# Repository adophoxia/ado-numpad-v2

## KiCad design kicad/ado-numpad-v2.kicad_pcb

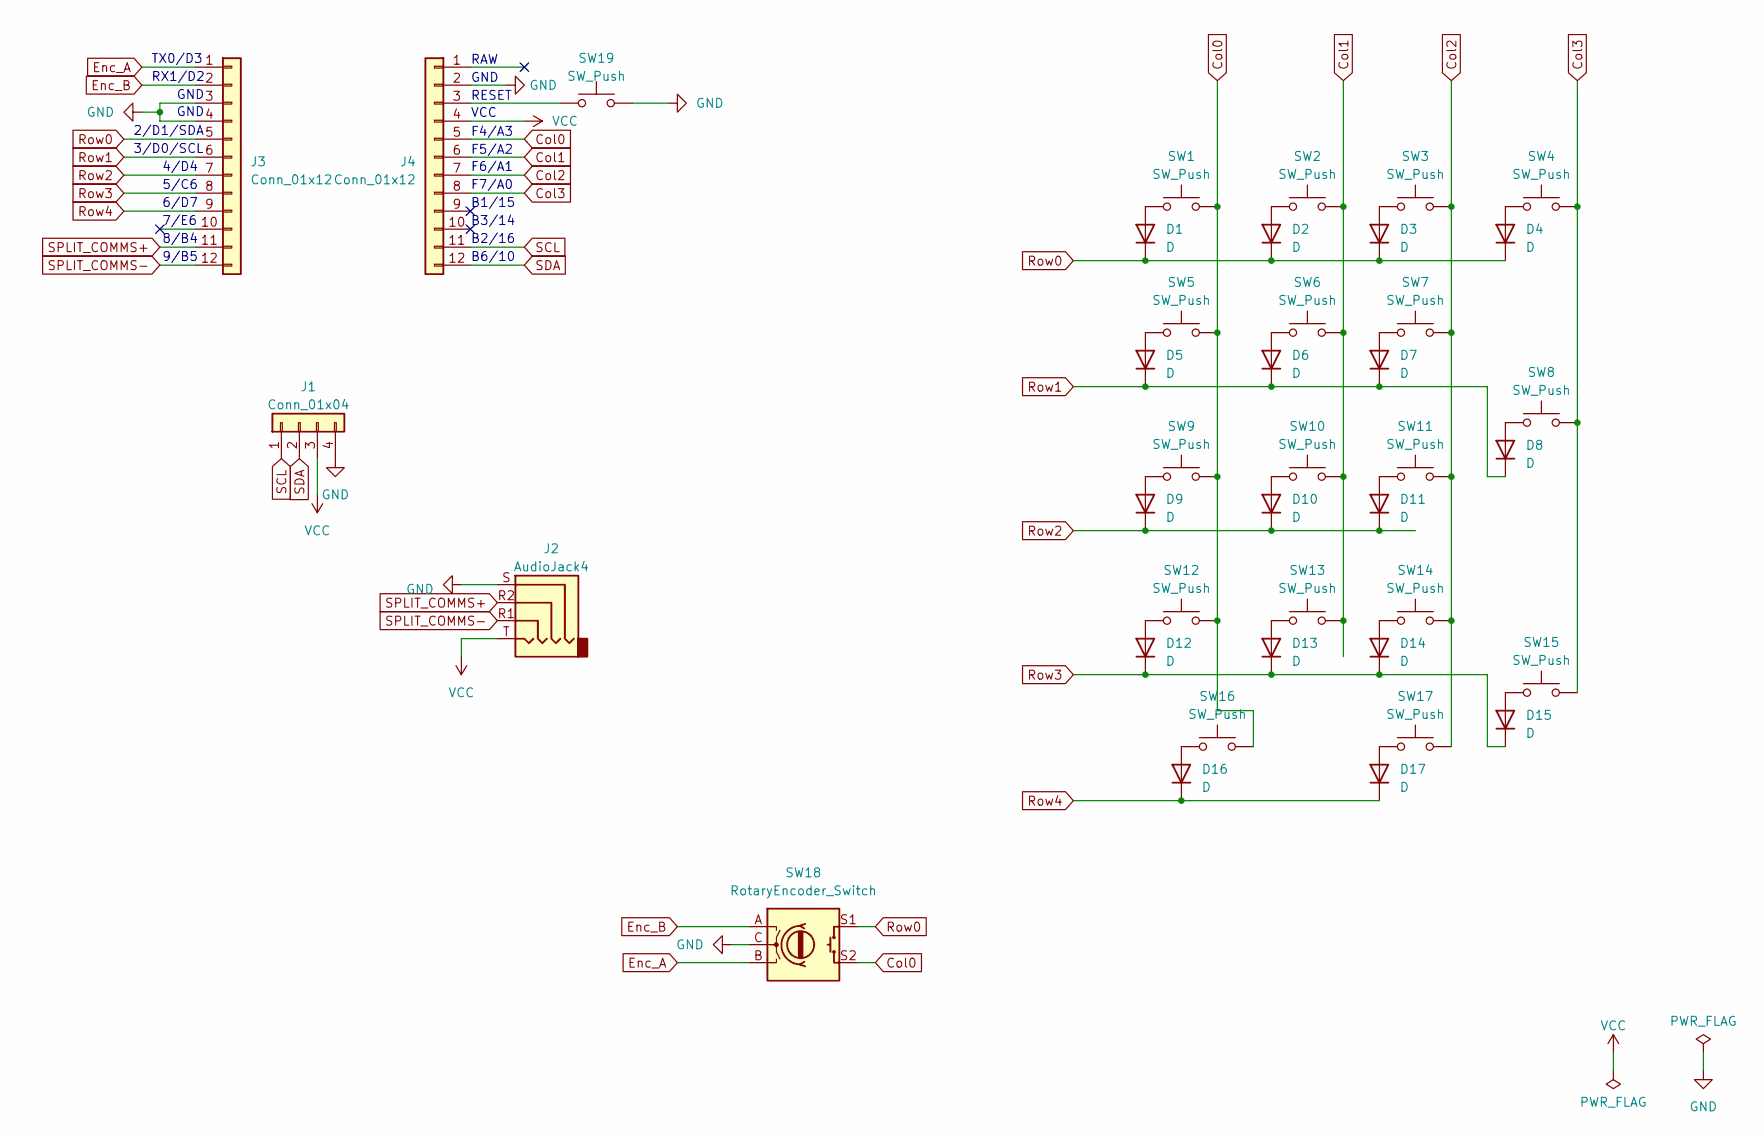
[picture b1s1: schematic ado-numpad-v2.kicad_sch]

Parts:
D1, D2, D3, D4, D5, D6, D7, D8, D9, D10, D11, D12, D13, D14, D15, D16, D17: D; D_DO-35_SOD27_P7.62mm_Horizontal
J1: Conn_01x04; PinSocket_1x04_P2.54mm_Vertical
J2: AudioJack4; Jack_3.5mm_KoreanHropartsElec_PJ-320D-4A_Horizontal
J3, J4: Conn_01x12; PinSocket_1x12_P2.54mm_Vertical
SW1, SW2, SW3, SW4, SW5, SW6, SW7, SW9, SW10, SW11, SW12, SW13, SW14, SW17: SW_Push; MX-Hotswap-1U
SW8, SW15, SW16: SW_Push; MX-Hotswap-2U-ReversedStabilizers
SW18: RotaryEncoder_Switch; RotaryEncoder_Alps_EC11E-Switch_Vertical_H20mm
SW19: SW_Push; SW_SPST_SKQG_WithStem

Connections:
Col0: J4.5, SW1.2, SW5.2, SW9.2, SW12.2, SW16.2, SW18.S2
Col1: J4.6, SW2.2, SW6.2, SW10.2, SW13.2
Col2: J4.7, SW3.2, SW7.2, SW11.2, SW14.2, SW17.2
Col3: J4.8, SW4.2, SW8.2, SW15.2
Enc_A: J3.1, SW18.B
Enc_B: J3.2, SW18.A
GND: J1.4, J2.S, J3.3, J3.4, J4.2, SW18.C, SW19.1
unnamed: D1.2 (A), SW1.1
unnamed: D2.2 (A), SW2.1
unnamed: D3.2 (A), SW3.1
unnamed: D4.2 (A), SW4.1
unnamed: D5.2 (A), SW5.1
unnamed: D6.2 (A), SW6.1
unnamed: D7.2 (A), SW7.1
unnamed: D8.2 (A), SW8.1
unnamed: D9.2 (A), SW9.1
unnamed: D10.2 (A), SW10.1
unnamed: D11.2 (A), SW11.1
unnamed: D12.2 (A), SW12.1
unnamed: D13.2 (A), SW13.1
unnamed: D14.2 (A), SW14.1
unnamed: D15.2 (A), SW15.1
unnamed: D16.2 (A), SW16.1
unnamed: D17.2 (A), SW17.1
unnamed: J4.3, SW19.2
Row0: D1.1 (K), D2.1 (K), D3.1 (K), D4.1 (K), J3.5, SW18.S1
Row1: D5.1 (K), D6.1 (K), D7.1 (K), D8.1 (K), J3.6
Row2: D9.1 (K), D10.1 (K), D11.1 (K), J3.7
Row3: D12.1 (K), D13.1 (K), D14.1 (K), D15.1 (K), J3.8
Row4: D16.1 (K), D17.1 (K), J3.9
SCL: J1.1, J4.11
SDA: J1.2, J4.12
SPLIT_COMMS+: J2.R2, J3.11
SPLIT_COMMS-: J2.R1, J3.12
VCC: J1.3, J2.T, J4.4

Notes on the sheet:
8/B4
3/D0/SCL
F7/A0
F6/A1
5/C6
B1/15
VCC
9/B5
GND
RAW
B3/14
B6/10
RESET
F4/A3
RX1/D2
2/D1/SDA
B2/16
6/D7
F5/A2
7/E6
4/D4
TX0/D3

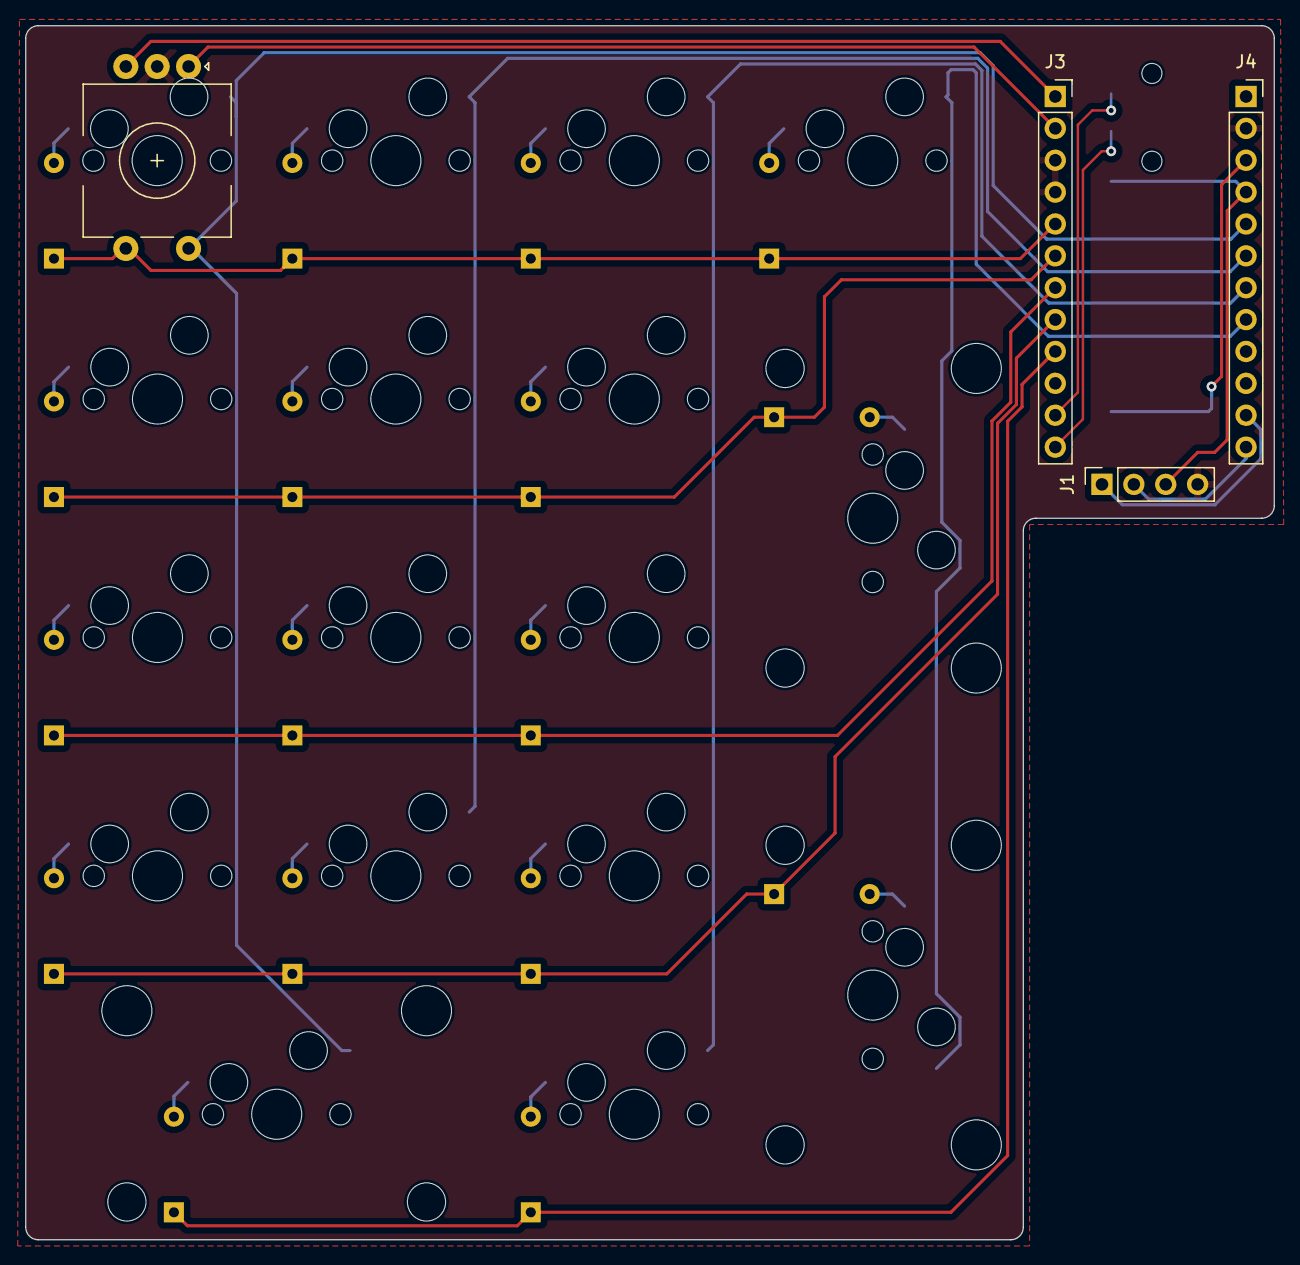
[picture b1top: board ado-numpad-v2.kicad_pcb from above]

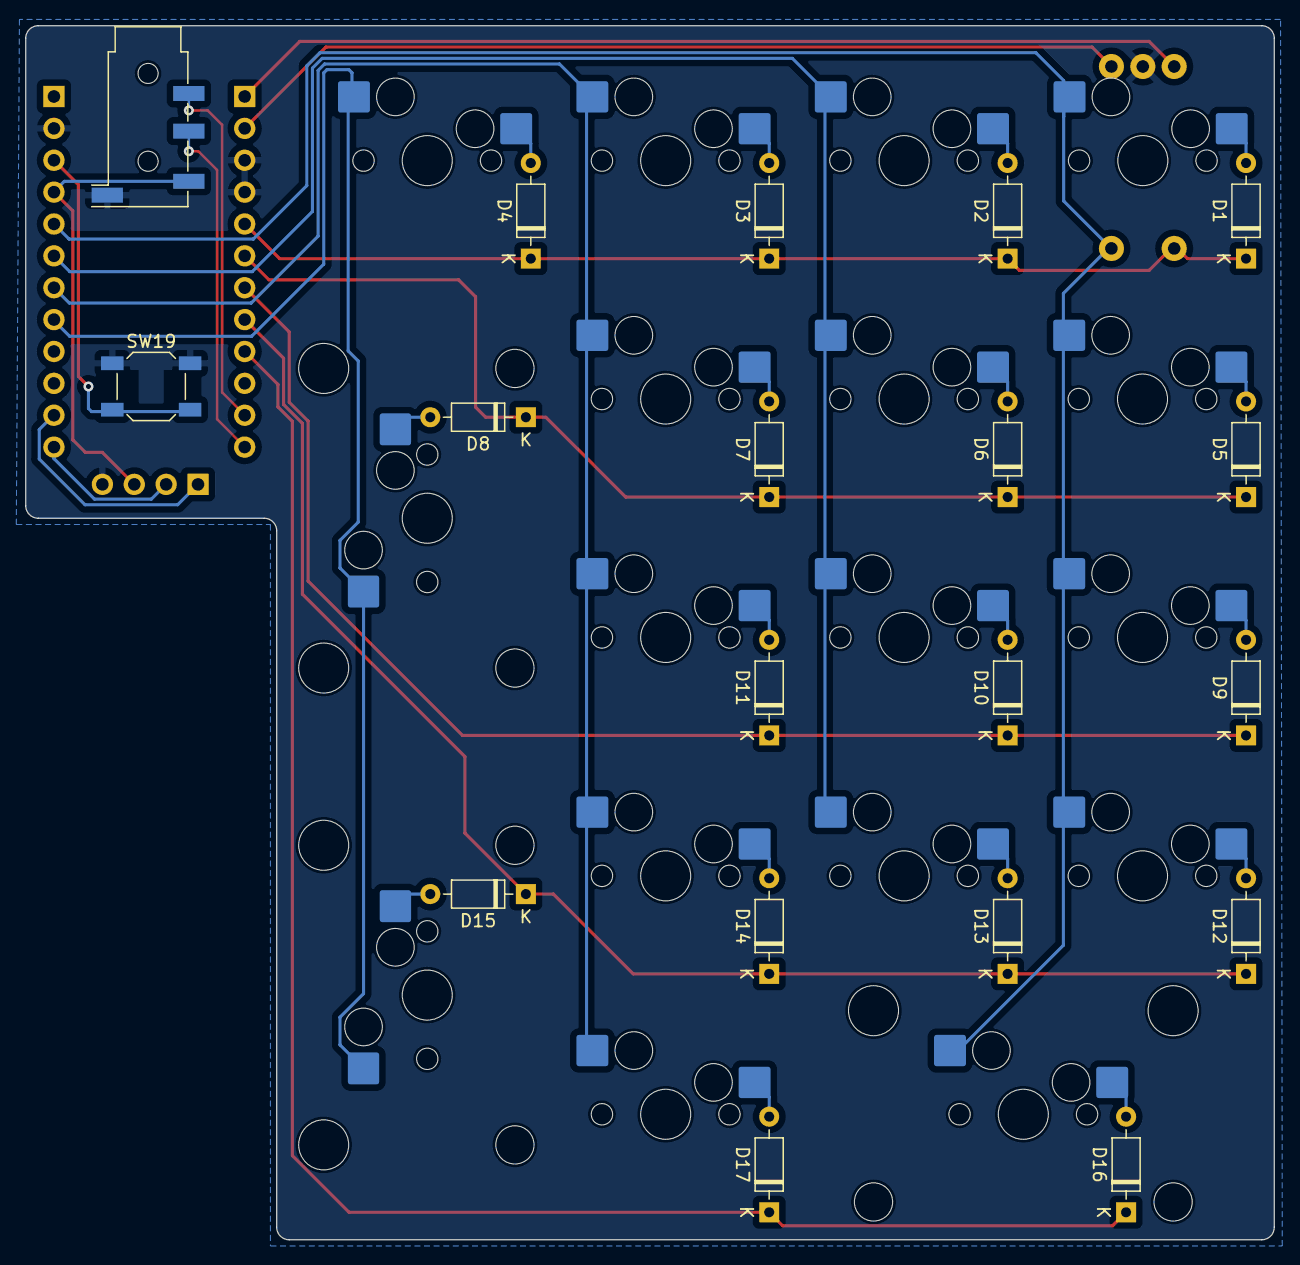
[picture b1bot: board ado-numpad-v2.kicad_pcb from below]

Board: 2 copper layers, 99.5 x 96.8 mm, 40 parts (19 on the bottom side), 35 nets.

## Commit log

2023-03-24 Add submodules
2023-03-24 Add project
2023-03-24 Create license
2023-03-24 Update to use 2 1x12_P2.54mm Pin Sockets
2023-03-25 Move Enc pins to Pin 1 and 2 on Pro Micro
